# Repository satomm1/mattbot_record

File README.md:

# Streaming Stereo Audio from I2S PCM Microphones to Nvidia Jetson Orin Nano

This repo contains code for streaming stereo audio from I2S PCM microphones to a Nvidia Jetson Orin Nano developer kit. In my case, I use a InvenSense ICS-43434 MEMS microphone. To convert the 24 bit PCM data output from the microphone to a form readable by the Jetson audio drivers, I use a PIC32MK0128MCA048T-I/Y8X microcontroller to convert the data to 32 bit and the correct endianness. 

Custom PCBs were designed to facilitate the MEMS microphones, PIC32, and connection to the Jetson. These PCBs were designed with KICAD and the designs (and KICAD files) are located in the `./pcb` directory. To order your own PCBs, the necessary gerber files are located in a `./pcb/*/gerber` directory. A BOM for each of the pcbs is also located in the directory (with part numbers for ordering from DigiKey).

The firmware for the PIC32 is located in the `./firmware` directory. This code should be loaded onto the PIC32 and supports sampling rates up to 44,100 Hz.

I include STL/Solidworks files for mounts for the microphones in the `./mounts` directory. These can be 3D printed. For a gasket, you can use a foam double sided tape found at a hardware store. For an acoustically transparent fabric to protect the port, I used muslin which can be found at a fabric store.

To enable the I2S on the Jetson, enable the I2S functionality via:
```
sudo python3 /opt/nvidia/jetson-io/jetson-io.py
```
As a simple test to see if the audio is working, you can use these commands to save a recording to `output.wav`:
```
amixer -c APE cset name="ADMAIF2 Mux" I2S2
arecord -D hw:APE,1 -r 16000 -c 2 -f S32_LE output.wav
```
Note, you will need to run the `amixer` command regardless before I2S audio will be read by the Jetson. It may also be necessary to run `python3 ./scripts/channels.py` to determine which audio device to use for the above example. If you find you need to change from `hw:APE,1` to something else, you will need to modify the other python files as well.

To use the I2S on the Nvidia Jetson with Python, you need to make sure you have installed the following packages:
```
pip install pyalsaaudio
sudo apt-get install libasound2-dev
sudo apt-get install alsa-utils
```
To test the python audio, run:
```
python3 ./scripts/record.py
```
which will save a short 5 second recording to `./scripts/output.wav`. To see the sound in frequency domain, you can run `./scripts/analyze_wav.py`.

We use a wakeword to determine when to start listening. The opensource [openWakeWord](https://github.com/dscripka/openWakeWord) is used to identify "Hey Robot," but the openWakeWord repo describes how to easily create your own wakeword. We also use the opensource [Silero voice activity detector](https://github.com/snakers4/silero-vad) to identify when speech has ended. Speech which is recorded is transcribed using [Whisper](https://github.com/openai/whisper). Recently, the transcription has been changed to [Faster Whisper](https://github.com/SYSTRAN/faster-whisper), which uses less computational resources. These features require the installation of additional dependencies:
```
pip install openwakeword
pip install silero-vad
pip install -U openai-whisper
pip install faster-whisper
```

Note: As of 12/7/2024, there is issues with the python package tokenizer version 0.21.0 for faster-whisper. I recommend installing an earlier version.

You will also need to download model files for openWakeWord. You can do this with `openwakeword.utils.download_models()` in python, or you can just run `./scripts/wakeword.py` which will also download the necessary model files.

Putting all this together, we create a function which:
1) Initializes the I2S interface on the Jetson.
2) Records audio using the I2S interface.
3) Detects the wakeword using openWakeWord.
4) Records speech until silence is detected using Silero VAD.
5) Saves the recorded audio to a file.
6) Transcribes the audio.
7) (optional) Sends the transcription to an LLM for a response.
Try it out using:
```
python3 ./scripts/get_audio_wakeword_speech_detection.py
```
This repo is set up as a ROS package compatible with ROS Noetic.

## Launching the Microphones
The relevant launch file is `audio_with_speech_detection.launch` which can be run with:
```
roslaunch mattbot_record audio_with_speech_detection.launch
```

### Wakeword audio save and upload

When `save_wakeword_audio:=true`, each completed post-wakeword utterance (the WAV sent to Whisper) is written to the **capture spool** as an upload-ready session — same layout as image capture:

```
{spool_dir}/robot_{ROBOT_ID}/{session_id}/
  manifest.json
  utterance.wav
```

Transcript and audio metadata are stored in `manifest.frames[0].extra`. Requires `ROBOT_ID` in the environment.

| Launch arg | Default | Description |
|------------|---------|-------------|
| `save_wakeword_audio` | `false` | Persist wakeword utterances to spool |
| `spool_dir` | `/workspace/catkin_ws/data/capture_spool` | Shared with `mattbot_capture` |

**Upload:** set `capture:=true` in bringup so `capture_uploader` scans the same spool. Example:

```bash
roslaunch mattbot_bringup tall.launch audio:=true capture:=true save_wakeword_audio:=true
```

`no_speech` aborts (wakeword with no following utterance) are not saved.

**Author**: Matthew Sato, Stanford Engineering Informatics Group

**License**: This package is released under an [MIT License](./LICENSE).

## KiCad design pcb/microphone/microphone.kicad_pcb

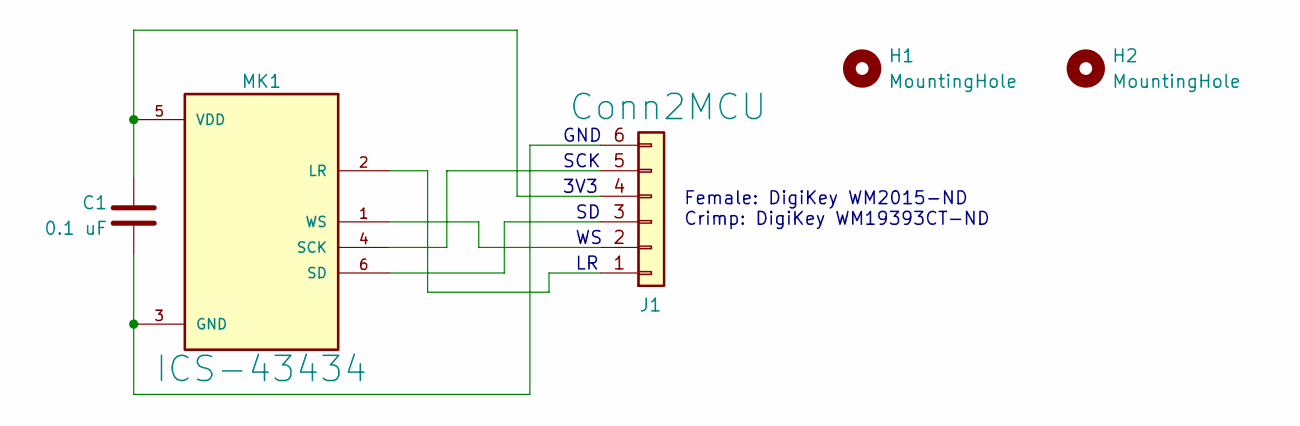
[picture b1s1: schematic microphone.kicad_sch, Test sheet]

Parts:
C1: 0.1 uF; C_0805_2012Metric_Pad1.18x1.45mm_HandSolder; Mfr P/N CL21B104KBCNNNC
H1, H2: MountingHole; MountingHole_3.2mm_M3
J1: Conn2MCU; CONN_22-05-3061_MOL; Mfr P/N 0022053061
MK1: ICS-43434; MIC_ICS-43434; Mfr P/N ICS-43434

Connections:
unnamed: J1.1, MK1.2 (LR)
unnamed: J1.2, MK1.1 (WS)
unnamed: J1.3, MK1.6 (SD)
unnamed: C1.1, J1.4, MK1.5 (VDD)
unnamed: J1.5, MK1.4 (SCK)
unnamed: C1.2, J1.6, MK1.3 (GND)

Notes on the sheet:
GND
Female: DigiKey WM2015-ND Crimp: DigiKey WM19393CT-ND
3V3
SCK

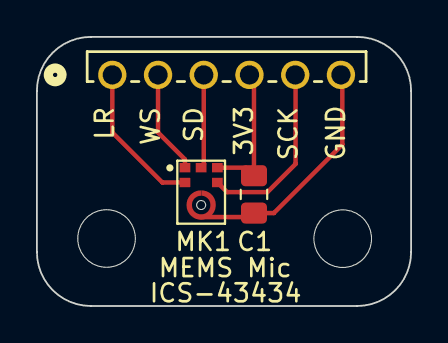
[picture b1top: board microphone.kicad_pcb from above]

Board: 2 copper layers, 20.8 x 15.0 mm, 5 parts (0 on the bottom side), 6 nets.

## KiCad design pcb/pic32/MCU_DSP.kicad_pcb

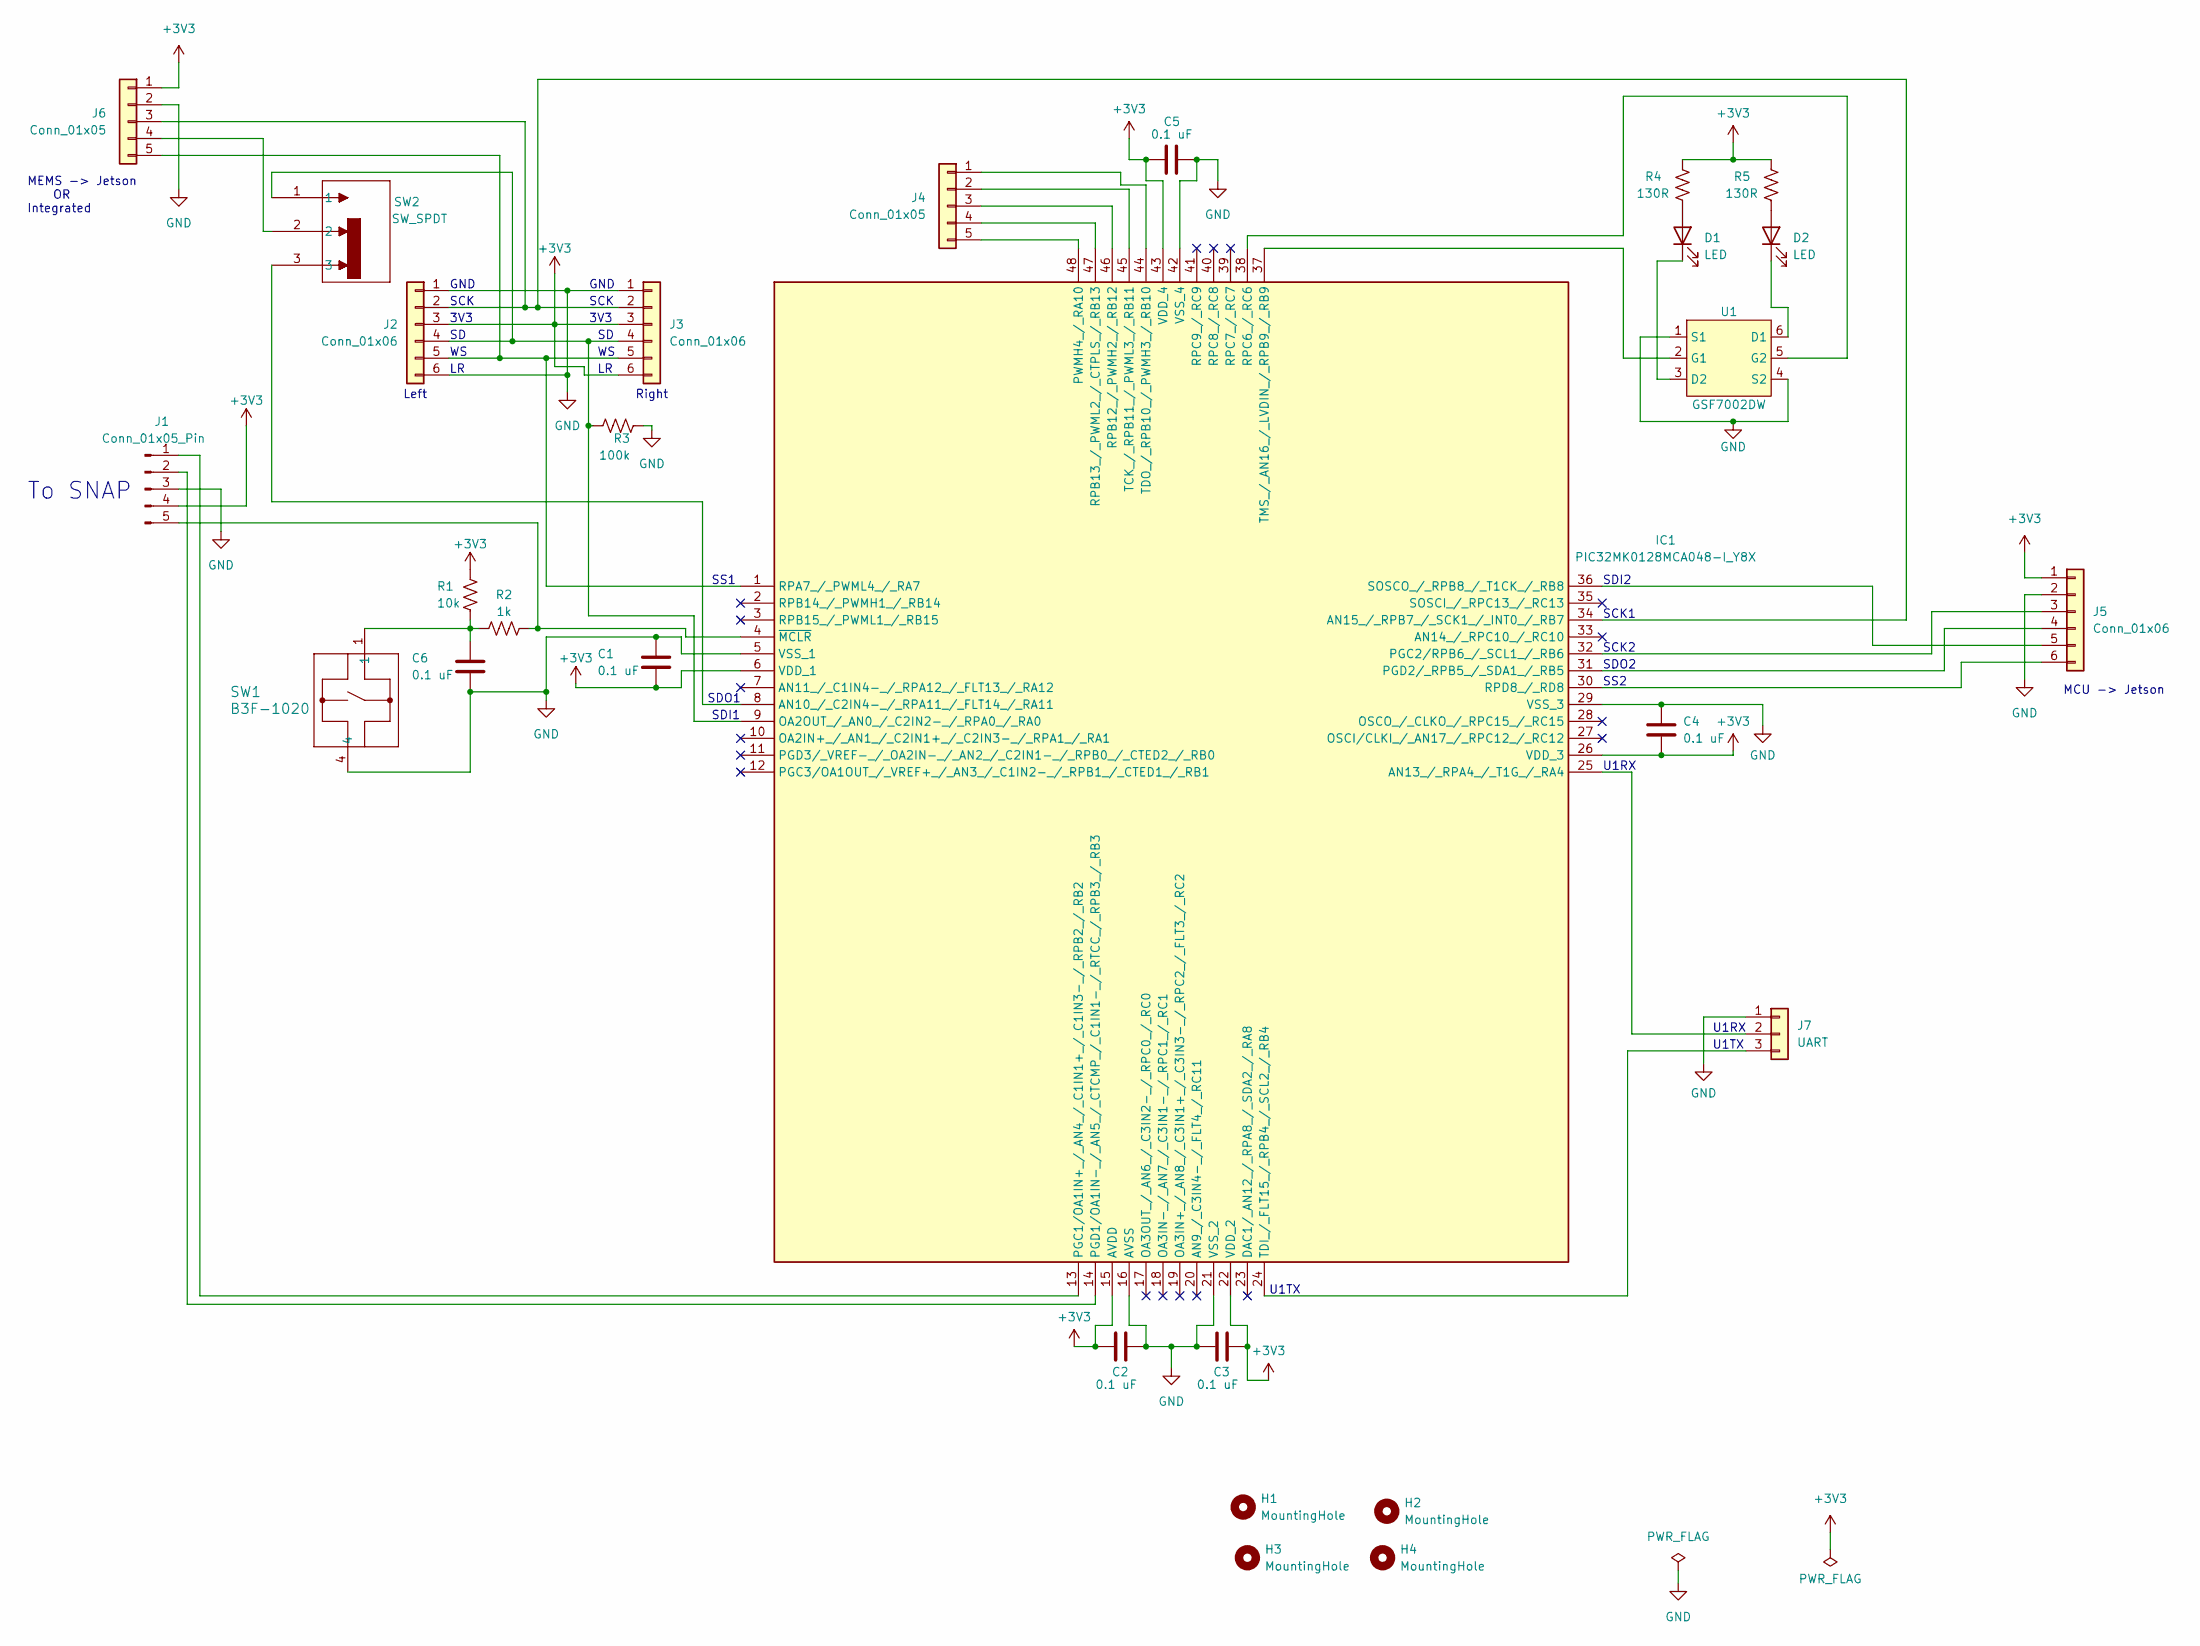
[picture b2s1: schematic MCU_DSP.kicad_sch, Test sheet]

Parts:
C1, C2, C3, C4, C5, C6: 0.1 uF; C_0805_2012Metric_Pad1.18x1.45mm_HandSolder; Mfr P/N CL21B104KBCNNNC
D1, D2: LED; LED_0805_2012Metric_Pad1.15x1.40mm_HandSolder; Mfr P/N 150080RS75000
H1, H2, H3, H4: MountingHole; MountingHole_3.2mm_M3
IC1: PIC32MK0128MCA048-I_Y8X; TQFP48_Y8X_MCH-M; Mfr P/N PIC32MK0128MCA048T-I/Y8X
J1: Conn_01x05_Pin; PinHeader_1x05_P2.54mm_Horizontal; Mfr P/N 10129379-910002BLF
J2, J3, J5: Conn_01x06; Molex_KK-254_AE-6410-06A_1x06_P2.54mm_Vertical; Mfr P/N 1718560006
J4: Conn_01x05; PinHeader_1x05_P2.54mm_Vertical
J6: Conn_01x05; Molex_KK-254_AE-6410-05A_1x05_P2.54mm_Vertical; Mfr P/N 1718560005
J7: UART; PinHeader_1x03_P2.54mm_Vertical
R1: 10k; R_0805_2012Metric_Pad1.20x1.40mm_HandSolder; Mfr P/N RMCF0805JT10K0
R2: 1k; R_0805_2012Metric_Pad1.20x1.40mm_HandSolder; Mfr P/N RMCF0805FT1K00
R3: 100k; R_0805_2012Metric_Pad1.20x1.40mm_HandSolder; Mfr P/N RMCF0805FG100K
R4, R5: 130R; R_0805_2012Metric_Pad1.20x1.40mm_HandSolder; Mfr P/N RMCF0805FT130R
SW1: B3F-1020; SW_B3F-1000_OMR; Mfr P/N B3F-1020
SW2: SW_SPDT; SPDT_OS102011_CNK; Mfr P/N OS102011MS2QN1
U1: GSF7002DW; SOT-363_SC-70-6; Mfr P/N GSF7002DW

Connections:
+3V3: C1.2, C2.1, C3.2, C4.2, C5.2, IC1.6 (VDD_1), IC1.15 (AVDD), IC1.22 (VDD_2), IC1.26 (VDD_3), IC1.43 (VDD_4), J1.4, J2.3, J3.3, J3.6, J5.1, J6.1, R1.1, R4.1, R5.1
GND: C1.1, C2.2, C3.1, C4.1, C5.1, C6.2, IC1.5 (VSS_1), IC1.16 (AVSS), IC1.21 (VSS_2), IC1.29 (VSS_3), IC1.42 (VSS_4), J1.3, J2.1, J2.6, J3.1, J5.2, J6.2, J7.1, R3.2, SW1.4, U1.1 (S1), U1.4 (S2)
unnamed: C6.1, R1.2, R2.1, SW1.1
unnamed: D1.2 (A), R4.2
unnamed: D1.1 (K), U1.3 (D2)
unnamed: D2.2 (A), R5.2
unnamed: D2.1 (K), U1.6 (D1)
unnamed: IC1.8 (AN10_/_C2IN4-_/_RPA11_/_FLT14_/_RA11), SW2.3
unnamed: IC1.25 (AN13_/_RPA4_/_T1G_/_RA4), J7.2
unnamed: IC1.34 (AN15_/_RPB7_/_SCK1_/_INT0_/_RB7), J2.2, J3.2, J6.3
unnamed: IC1.9 (OA2OUT_/_AN0_/_C2IN2-_/_RPA0_/_RA0), J2.4, J3.4, R3.1, SW2.1
unnamed: IC1.13 (PGC1/OA1IN+_/_AN4_/_C1IN1+_/_C1IN3-_/_R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), J1.1
unnamed: IC1.32 (PGC2/RPB6_/_SCL1_/_RB6), J5.3
unnamed: IC1.14 (PGD1/OA1IN-_/_AN5_/_CTCMP_/_C1IN1-_/_RT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), J1.2
unnamed: IC1.31 (PGD2/_RPB5_/_SDA1_/_RB5), J5.4
unnamed: IC1.48 (PWMH4_/_RA10), J4.5
unnamed: IC1.1 (RPA7_/_PWML4_/_RA7), J2.5, J3.5, J6.5
unnamed: IC1.46 (RPB12_/_PWMH2_/_RB12), J4.3
unnamed: IC1.47 (RPB13_/_PWML2_/_CTPLS_/_RB13), J4.4
unnamed: IC1.38 (RPC6_/_RC6), U1.5 (G2)
unnamed: IC1.30 (RPD8_/_RD8), J5.6
unnamed: IC1.36 (SOSCO_/_RPB8_/_T1CK_/_RB8), J5.5
unnamed: IC1.45 (TCK_/_RPB11_/_PWML3_/_RB11), J4.2
unnamed: IC1.24 (TDI_/_FLT15_/_RPB4_/_SCL2_/_RB4), J7.3
unnamed: IC1.44 (TDO_/_RPB10_/_PWMH3_/_RB10), J4.1
unnamed: IC1.37 (TMS_/_AN16_/_LVDIN_/_RPB9_/_RB9), U1.2 (G1)
unnamed: IC1.4 (~MCLR), J1.5, R2.2
unnamed: J6.4, SW2.2

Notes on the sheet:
SCK
3V3
U1TX
SS2
GND
MCU -> Jetson
SDO2
SDI2
U1RX
SCK2
SS1
Left
MEMS -> Jetson OR Integrated
To SNAP
SDO1
Right
SDI1
SCK1

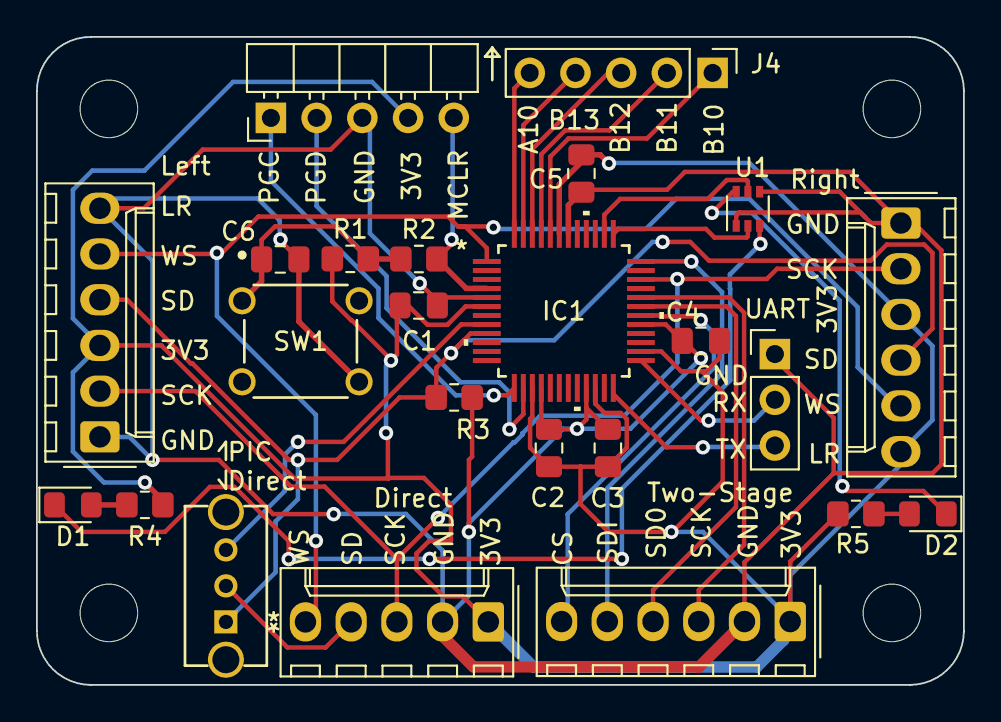
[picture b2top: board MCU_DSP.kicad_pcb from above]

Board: 2 copper layers, 51.5 x 36.0 mm, 28 parts (0 on the bottom side), 28 nets.

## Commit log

2024-10-04 Add minimal code for i2s control from python
2024-10-21 Add files to test I2S. Some are working, but sampling rate is off
2024-10-28 Add code for recording and transcribing on button command
2024-10-29 Code for basic recording of audio from microphone
2024-10-29 Add some documentation
2024-10-30 Improve analysis of sound
2024-10-31 Plot both channels
2024-10-31 Fine tune audio recording and connection with whisper
2024-11-02 Wakeword detection
2024-11-02 Get the wakeword and transcription working together
2024-11-04 Custom wakeword, avoid wakeword detection immediately after recording
2024-11-04 Feed audio transcription to gemini
2024-11-04 Begin readme
2024-11-05 Add files to make package
2024-11-05 Attempt to do speech detection
2024-11-05 Improvements to wakeword speech detection
2024-11-05 Increase gain
2024-11-05 Fix wakeword detection
2024-11-06 normalize data before speech detection, still some errors
2024-11-06 Look for gaps in speech to determine when to stop the recording.
2024-11-06 Get launch files working
2024-11-07 Add readme and other files
2024-11-07 Add license in readme
2024-11-07 Finish readme
2024-11-07 Debug and get running smoothly
2024-11-08 Update the readme with a few new instructions
2024-11-16 Update to use faster-whisper since whisper is too heavy
2024-11-18 Handle exceptions if gemini endpoint not running
2024-12-08 Add note about package installation
2024-12-09 Handle case of when asking for goals
2024-12-18 Change goal topic that we publish to
2025-05-27 Remove some unused code
2025-05-28 Correct the printing of the response
2025-06-02 Skip audio processing when moving
2025-06-04 Print results without crashing (due to json formatting)
2025-06-12 Add 1 second sleep when moving and not processing
2025-07-02 Download mel sprectrograph is doesnot exist
2025-07-02 Add onnx ability for wakeword (but don't use it)
2025-07-06 Allow for goal to be name based.
2025-11-07 Handle the rendezvous command
2026-06-24 Stop tracking audio_data.png plot
2026-06-24 Auto-detect ALSA capture device from APE mixer routing.
    Inline device resolution in the speech detection node so roslaunch does not depend on extra modules, and ignore Python bytecode in git.
2026-06-25 Add wakeword audio saving and upload functionality
2026-06-25 Fix problem of automatic no speech detected
2026-06-25 Add tf dependency and implement pose lookup in audio recording
